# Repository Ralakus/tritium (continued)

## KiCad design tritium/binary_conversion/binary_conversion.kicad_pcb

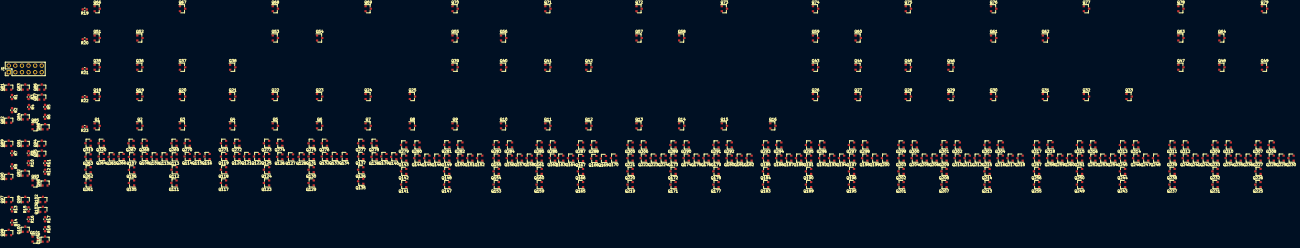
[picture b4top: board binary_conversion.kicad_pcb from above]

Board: 2 copper layers, 339 parts (0 on the bottom side), 146 nets, no tracks yet.

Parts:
J1: 2x6 Odd Even Header 2.54mm; PinHeader_2x06_P2.54mm_Vertical
Q1, Q2, Q3, Q4, Q5, Q6, Q7, Q8, Q9, Q10, Q11, Q12, Q13, Q14, Q15, Q16, Q18, Q19, Q20, Q21, Q22, Q23, Q24, Q25, Q26, Q27, Q28, Q29, Q30, Q31, Q32, Q33, Q35, Q36, Q37, Q38, Q39, Q40, Q41, Q42, Q43, Q44, Q45, Q46, Q47, Q48, Q49, Q51, Q52, Q53, Q54, Q55, Q56, Q57, Q58, Q59, Q60, Q61, Q62, Q63, Q64, Q66, Q67, Q68, Q69, Q70, Q71, Q72, Q73, Q74, Q75, Q76, Q77, Q78, Q79, Q82, Q84, Q85, Q88, Q90, Q92, Q93, Q96, Q98, Q100, Q101, Q104, Q108, Q109, Q110, Q114, Q115, Q116, Q120, Q121, Q122, Q126, Q127, Q128, Q132, Q133, Q134, Q138, Q139, Q140, Q144, Q145, Q146, Q150, Q151, Q152, Q156, Q157, Q158, Q162, Q163, Q164, Q168, Q169, Q170, Q174, Q175, Q176, Q180, Q181, Q182, Q186, Q187, Q188, Q192, Q193, Q194, Q198, Q199, Q200, Q204, Q205, Q206, Q210, Q211, Q212, Q216, Q217, Q218, Q222, Q223, Q224, Q228, Q229, Q230, Q234, Q235, Q236, Q240, Q241, Q242, Q246, Q247, Q248, Q252, Q253, Q254, Q258, Q259, Q260, Q264, Q265, Q266, Q268, Q270, Q272, Q274, Q276, Q278, Q280, Q282, Q284, Q286, Q288, Q290, Q292, Q294, Q296, Q298, Q300, Q302, Q304, Q306, Q308, Q310, Q312, Q314, Q316, Q318, Q320: 2N7002; SOT-23
Q81, Q83, Q86, Q87, Q89, Q91, Q94, Q95, Q97, Q99, Q102, Q103, Q105, Q106, Q107, Q111, Q112, Q113, Q117, Q118, Q119, Q123, Q124, Q125, Q129, Q130, Q131, Q135, Q136, Q137, Q141, Q142, Q143, Q147, Q148, Q149, Q153, Q154, Q155, Q159, Q160, Q161, Q165, Q166, Q167, Q171, Q172, Q173, Q177, Q178, Q179, Q183, Q184, Q185, Q189, Q190, Q191, Q195, Q196, Q197, Q201, Q202, Q203, Q207, Q208, Q209, Q213, Q214, Q215, Q219, Q220, Q221, Q225, Q226, Q227, Q231, Q232, Q233, Q237, Q238, Q239, Q243, Q244, Q245, Q249, Q250, Q251, Q255, Q256, Q257, Q261, Q262, Q263, Q267, Q269, Q271, Q273, Q275, Q277, Q279, Q281, Q283, Q285, Q287, Q289, Q291, Q293, Q295, Q297, Q299, Q301, Q303, Q305, Q307, Q309, Q311, Q313, Q315, Q317, Q319: BSS84; SOT-23
R1, R2, R3, R4, R5, R6, R7, R8, R9, R10, R11, R12, R13, R14, R15, R16, R17, R18, R19, R20, R21, R22, R23: 12k; R_0603_1608Metric

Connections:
/000/Out: Q14.1, Q58.1, Q289.2, Q290.3
/000/Sheet6206C5A9/In: Q171.2, Q172.2, Q173.2, Q174.3, Q289.1, Q290.1
/0i0/B: Q90.3, Q93.1, Q95.1, Q106.1, Q109.1, Q112.1, Q115.1, Q154.1, Q157.1, Q160.1, Q163.1, Q166.1, Q169.1, Q202.1, Q205.1, Q208.1, Q211.1, Q214.1, Q217.1, Q262.1, Q265.1, R8.2
/0i0/Out: Q11.1, Q41.1, Q71.1, Q285.2, Q286.3
/0i0/Sheet6206C5A9/In: Q159.2, Q160.2, Q161.2, Q162.3, Q285.1, Q286.1
/0i1/Out: Q12.1, Q42.1, Q287.2, Q288.3
/0i1/Sheet6206C5A9/In: Q165.2, Q166.2, Q167.2, Q168.3, Q287.1, Q288.1
/00i/C: Q82.3, Q85.1, Q87.1, Q119.1, Q122.1, Q137.1, Q140.1, Q155.1, Q158.1, Q185.1, Q188.1, Q203.1, Q206.1, Q221.1, Q224.1, Q239.1, Q242.1, Q257.1, Q260.1, Q263.1, Q266.1, R2.2
/00i/Out: Q13.1, Q57.1, Q72.1, Q305.2, Q306.3
/00i/Sheet6206C5A9/In: Q219.2, Q220.2, Q221.2, Q222.3, Q305.1, Q306.1
/0ii/Out: Q10.1, Q40.1, Q56.1, Q283.2, Q284.3
/0ii/Sheet6206C5A9/In: Q153.2, Q154.2, Q155.2, Q156.3, Q283.1, Q284.1
/001/Out: Q15.1, Q73.1, Q291.2, Q292.3
/001/Sheet6206C5A9/In: Q177.2, Q178.2, Q179.2, Q180.3, Q291.1, Q292.1
/1i0/Out: Q29.1, Q46.1, Q301.2, Q302.3
/1i0/Sheet6206C5A9/In: Q207.2, Q208.2, Q209.2, Q210.3, Q301.1, Q302.1
/1i1/Out: Q30.1, Q61.1, Q76.1, Q303.2, Q304.3
/1i1/Sheet6206C5A9/In: Q213.2, Q214.2, Q215.2, Q216.3, Q303.1, Q304.1
/01i/Out: Q16.1, Q293.2, Q294.3
/01i/Sheet6206C5A9/In: Q183.2, Q184.2, Q185.2, Q186.3, Q293.1, Q294.1
/1ii/Out: Q28.1, Q45.1, Q75.1, Q299.2, Q300.3
/1ii/Sheet6206C5A9/In: Q201.2, Q202.2, Q203.2, Q204.3, Q299.1, Q300.1
/010/Out: Q26.1, Q43.1, Q59.1, Q74.1, Q295.2, Q296.3
/010/Sheet6206C5A9/In: Q189.2, Q190.2, Q191.2, Q192.3, Q295.1, Q296.1
/10i/Out: Q31.1, Q62.1, Q317.2, Q318.3
/10i/Sheet6206C5A9/In: Q255.2, Q256.2, Q257.2, Q258.3, Q317.1, Q318.1
/011/Out: Q27.1, Q44.1, Q60.1, Q297.2, Q298.3
/011/Sheet6206C5A9/In: Q195.2, Q196.2, Q197.2, Q198.3, Q297.1, Q298.1
/11i/Out: Q47.1, Q63.1, Q78.1, Q311.2, Q312.3
/11i/Sheet6206C5A9/In: Q237.2, Q238.2, Q239.2, Q240.3, Q311.1, Q312.1
/100/Out: Q32.1, Q77.1, Q315.2, Q316.3
/100/Sheet6206C5A9/In: Q249.2, Q250.2, Q251.2, Q252.3, Q315.1, Q316.1
/101/Out: Q33.1, Q313.2, Q314.3
/101/Sheet6206C5A9/In: Q243.2, Q244.2, Q245.2, Q246.3, Q313.1, Q314.1
/110/Out: Q48.1, Q64.1, Q309.2, Q310.3
/110/Sheet6206C5A9/In: Q231.2, Q232.2, Q233.2, Q234.3, Q309.1, Q310.1
/111/Out: Q49.1, Q79.1, Q307.2, Q308.3
/111/Sheet6206C5A9/In: Q225.2, Q226.2, Q227.2, Q228.3, Q307.1, Q308.1
/decoder0/0: Q107.1, Q110.1, Q125.1, Q128.1, Q143.1, Q146.1, Q161.1, Q164.1, Q173.1, Q176.1, Q191.1, Q194.1, Q209.1, Q212.1, Q233.1, Q236.1, Q251.1, Q254.1, R5.2, R6.1
/decoder0/1: Q86.1, Q88.1, Q113.1, Q116.1, Q131.1, Q134.1, Q149.1, Q152.1, Q167.1, Q170.1, Q179.1, Q182.1, Q197.1, Q200.1, Q215.1, Q218.1, Q227.1, Q230.1, Q245.1, Q248.1, R3.2, R4.1
/decoder0/inverter/In: Q81.2, Q83.1, Q84.1, R1.1
/decoder0/inverter/Nti: Q84.3, R4.2
/decoder0/inverter/Pti: Q83.2, R3.1
/decoder1/0: Q118.1, Q121.1, Q124.1, Q127.1, Q130.1, Q133.1, Q172.1, Q175.1, Q178.1, Q181.1, Q220.1, Q223.1, Q244.1, Q247.1, Q250.1, Q253.1, Q256.1, Q259.1, R11.2, R12.1
/decoder1/1: Q94.1, Q96.1, Q136.1, Q139.1, Q142.1, Q145.1, Q148.1, Q151.1, Q184.1, Q187.1, Q190.1, Q193.1, Q196.1, Q199.1, Q226.1, Q229.1, Q232.1, Q235.1, Q238.1, Q241.1, R9.2, R10.1
/decoder1/inverter/In: Q89.2, Q91.1, Q92.1, R7.1
/decoder1/inverter/Nti: Q92.3, R10.2
/decoder1/inverter/Pti: Q91.2, R9.1
/decoder2/0: Q153.1, Q156.1, Q159.1, Q162.1, Q165.1, Q168.1, Q171.1, Q174.1, Q177.1, Q180.1, Q183.1, Q186.1, Q189.1, Q192.1, Q195.1, Q198.1, Q219.1, Q222.1, R17.2, R18.1
/decoder2/1: Q102.1, Q104.1, Q201.1, Q204.1, Q207.1, Q210.1, Q213.1, Q216.1, Q225.1, Q228.1, Q231.1, Q234.1, Q237.1, Q240.1, Q243.1, Q246.1, Q249.1, Q252.1, Q255.1, Q258.1, R15.2, R16.1
/decoder2/inverter/In: Q97.2, Q99.1, Q100.1, R13.1
/decoder2/inverter/Nti: Q100.3, R16.2
/decoder2/inverter/Pti: Q99.2, R15.1
/i00/A: Q98.3, Q101.1, Q103.1, Q105.1, Q108.1, Q111.1, Q114.1, Q117.1, Q120.1, Q123.1, Q126.1, Q129.1, Q132.1, Q135.1, Q138.1, Q141.1, Q144.1, Q147.1, Q150.1, Q261.1, Q264.1, R14.2
/i00/Out: Q5.1, Q22.1, Q53.1, Q68.1, Q273.2, Q274.3
/i00/Sheet6206C5A9/In: Q123.2, Q124.2, Q125.2, Q126.3, Q273.1, Q274.1
/i0i/Out: Q4.1, Q21.1, Q38.1, Q271.2, Q272.3
/i0i/Sheet6206C5A9/In: Q117.2, Q118.2, Q119.2, Q120.3, Q271.1, Q272.1
/i01/Out: Q6.1, Q23.1, Q54.1, Q275.2, Q276.3
/i01/Sheet6206C5A9/In: Q129.2, Q130.2, Q131.2, Q132.3, Q275.1, Q276.1
/i1i/Out: Q7.1, Q24.1, Q69.1, Q277.2, Q278.3
/i1i/Sheet6206C5A9/In: Q135.2, Q136.2, Q137.2, Q138.3, Q277.1, Q278.1
/i10/Out: Q8.1, Q25.1, Q279.2, Q280.3
/i10/Sheet6206C5A9/In: Q141.2, Q142.2, Q143.2, Q144.3, Q279.1, Q280.1
/i11/Out: Q9.1, Q39.1, Q55.1, Q70.1, Q281.2, Q282.3
/i11/Sheet6206C5A9/In: Q147.2, Q148.2, Q149.2, Q150.3, Q281.1, Q282.1
/ii0/Out: Q2.1, Q19.1, Q36.1, Q52.1, Q267.2, Q268.3
/ii0/Sheet6206C5A9/In: Q105.2, Q106.2, Q107.2, Q108.3, Q267.1, Q268.1
/ii1/Out: Q3.1, Q20.1, Q37.1, Q67.1, Q269.2, Q270.3
/ii1/Sheet6206C5A9/In: Q111.2, Q112.2, Q113.2, Q114.3, Q269.1, Q270.1
/iii/Out: Q1.1, Q18.1, Q35.1, Q51.1, Q66.1, Q319.2, Q320.3
/iii/Sheet6206C5A9/In: Q261.2, Q262.2, Q263.2, Q264.3, Q319.1, Q320.1
B0: J1.10, Q66.3, Q67.3, Q68.3, Q69.3, Q70.3, Q71.3, Q72.3, Q73.3, Q74.3, Q75.3, Q76.3, Q77.3, Q78.3, Q79.3, R19.1
B1: J1.8, Q51.3, Q52.3, Q53.3, Q54.3, Q55.3, Q56.3, Q57.3, Q58.3, Q59.3, Q60.3, Q61.3, Q62.3, Q63.3, Q64.3, R20.1
B2: J1.6, Q35.3, Q36.3, Q37.3, Q38.3, Q39.3, Q40.3, Q41.3, Q42.3, Q43.3, Q44.3, Q45.3, Q46.3, Q47.3, Q48.3, Q49.3, R21.1
B3: J1.4, Q18.3, Q19.3, Q20.3, Q21.3, Q22.3, Q23.3, Q24.3, Q25.3, Q26.3, Q27.3, Q28.3, Q29.3, Q30.3, Q31.3, Q32.3, Q33.3, R22.1
B4: J1.2, Q1.3, Q2.3, Q3.3, Q4.3, Q5.3, Q6.3, Q7.3, Q8.3, Q9.3, Q10.3, Q11.3, Q12.3, Q13.3, Q14.3, Q15.3, Q16.3, R23.1
GND: J1.1, Q1.2, Q2.2, Q3.2, Q4.2, Q5.2, Q6.2, Q7.2, Q8.2, Q9.2, Q10.2, Q11.2, Q12.2, Q13.2, Q14.2, Q15.2, Q16.2, Q18.2, Q19.2, Q20.2, Q21.2, Q22.2, Q23.2, Q24.2, Q25.2, Q26.2, Q27.2, Q28.2, Q29.2, Q30.2, Q31.2, Q32.2, Q33.2, Q35.2, Q36.2, Q37.2, Q38.2, Q39.2, Q40.2, Q41.2, Q42.2, Q43.2, Q44.2, Q45.2, Q46.2, Q47.2, Q48.2, Q49.2, Q51.2, Q52.2, Q53.2, Q54.2, Q55.2, Q56.2, Q57.2, Q58.2, Q59.2, Q60.2, Q61.2, Q62.2, Q63.2, Q64.2, Q66.2, Q67.2, Q68.2, Q69.2, Q70.2, Q71.2, Q72.2, Q73.2, Q74.2, Q75.2, Q76.2, Q77.2, Q78.2, Q79.2, Q110.2, Q116.2, Q122.2, Q128.2, Q134.2, Q140.2, Q146.2, Q152.2, Q158.2, Q164.2, Q170.2, Q176.2, Q182.2, Q188.2, Q194.2, Q200.2, Q206.2, Q212.2, Q218.2, Q224.2, Q230.2, Q236.2, Q242.2, Q248.2, Q254.2, Q260.2, Q266.2, Q268.2, Q270.2, Q272.2, Q274.2, Q276.2, Q278.2, Q280.2, Q282.2, Q284.2, Q286.2, Q288.2, Q290.2, Q292.2, Q294.2, Q296.2, Q298.2, Q300.2, Q302.2, Q304.2, Q306.2, Q308.2, Q310.2, Q312.2, Q314.2, Q316.2, Q318.2, Q320.2
unnamed: Q85.3, Q88.3, R6.2
unnamed: Q86.2, Q87.3
unnamed: Q87.2, R5.1
unnamed: Q93.3, Q96.3, R12.2
unnamed: Q94.2, Q95.3
unnamed: Q95.2, R11.1
unnamed: Q101.3, Q104.3, R18.2
unnamed: Q102.2, Q103.3
unnamed: Q103.2, R17.1
unnamed: Q108.2, Q109.3
unnamed: Q109.2, Q110.3
unnamed: Q114.2, Q115.3
unnamed: Q115.2, Q116.3
unnamed: Q120.2, Q121.3
unnamed: Q121.2, Q122.3
unnamed: Q126.2, Q127.3
unnamed: Q127.2, Q128.3
unnamed: Q132.2, Q133.3
unnamed: Q133.2, Q134.3
unnamed: Q138.2, Q139.3
unnamed: Q139.2, Q140.3
unnamed: Q144.2, Q145.3
unnamed: Q145.2, Q146.3
unnamed: Q150.2, Q151.3
unnamed: Q151.2, Q152.3
unnamed: Q156.2, Q157.3
unnamed: Q157.2, Q158.3
unnamed: Q162.2, Q163.3
unnamed: Q163.2, Q164.3
unnamed: Q168.2, Q169.3
unnamed: Q169.2, Q170.3
unnamed: Q174.2, Q175.3
unnamed: Q175.2, Q176.3
unnamed: Q180.2, Q181.3
unnamed: Q181.2, Q182.3
unnamed: Q186.2, Q187.3
unnamed: Q187.2, Q188.3
unnamed: Q192.2, Q193.3
unnamed: Q193.2, Q194.3
unnamed: Q198.2, Q199.3
unnamed: Q199.2, Q200.3
unnamed: Q204.2, Q205.3
unnamed: Q205.2, Q206.3
unnamed: Q210.2, Q211.3
unnamed: Q211.2, Q212.3
unnamed: Q216.2, Q217.3
unnamed: Q217.2, Q218.3
unnamed: Q222.2, Q223.3
unnamed: Q223.2, Q224.3
unnamed: Q228.2, Q229.3
unnamed: Q229.2, Q230.3
unnamed: Q234.2, Q235.3
unnamed: Q235.2, Q236.3
unnamed: Q240.2, Q241.3
unnamed: Q241.2, Q242.3
unnamed: Q246.2, Q247.3
unnamed: Q247.2, Q248.3
unnamed: Q252.2, Q253.3
unnamed: Q253.2, Q254.3
unnamed: Q258.2, Q259.3
unnamed: Q259.2, Q260.3
unnamed: Q264.2, Q265.3
unnamed: Q265.2, Q266.3
T0: J1.11, Q81.1, Q82.1
T1: J1.9, Q89.1, Q90.1
T2: J1.7, Q97.1, Q98.1
Vdd: J1.3, Q81.3, Q83.3, Q86.3, Q89.3, Q91.3, Q94.3, Q97.3, Q99.3, Q102.3, Q105.3, Q106.3, Q107.3, Q111.3, Q112.3, Q113.3, Q117.3, Q118.3, Q119.3, Q123.3, Q124.3, Q125.3, Q129.3, Q130.3, Q131.3, Q135.3, Q136.3, Q137.3, Q141.3, Q142.3, Q143.3, Q147.3, Q148.3, Q149.3, Q153.3, Q154.3, Q155.3, Q159.3, Q160.3, Q161.3, Q165.3, Q166.3, Q167.3, Q171.3, Q172.3, Q173.3, Q177.3, Q178.3, Q179.3, Q183.3, Q184.3, Q185.3, Q189.3, Q190.3, Q191.3, Q195.3, Q196.3, Q197.3, Q201.3, Q202.3, Q203.3, Q207.3, Q208.3, Q209.3, Q213.3, Q214.3, Q215.3, Q219.3, Q220.3, Q221.3, Q225.3, Q226.3, Q227.3, Q231.3, Q232.3, Q233.3, Q237.3, Q238.3, Q239.3, Q243.3, Q244.3, Q245.3, Q249.3, Q250.3, Q251.3, Q255.3, Q256.3, Q257.3, Q261.3, Q262.3, Q263.3, Q267.3, Q269.3, Q271.3, Q273.3, Q275.3, Q277.3, Q279.3, Q281.3, Q283.3, Q285.3, Q287.3, Q289.3, Q291.3, Q293.3, Q295.3, Q297.3, Q299.3, Q301.3, Q303.3, Q305.3, Q307.3, Q309.3, Q311.3, Q313.3, Q315.3, Q317.3, Q319.3, R2.1, R8.1, R14.1, R19.2, R20.2, R21.2, R22.2, R23.2
Vss: J1.5, Q82.2, Q84.2, Q85.2, Q88.2, Q90.2, Q92.2, Q93.2, Q96.2, Q98.2, Q100.2, Q101.2, Q104.2, R1.2, R7.2, R13.2
